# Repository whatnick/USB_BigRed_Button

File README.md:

# KiCAD port of USB Big Red Button Project
- Imported from Eagle version of files on 28/11/2020
- Added STL enclosure / PCB carries 24/12/2020
- For mechanical designs in Fusion 360 refer to original repository
- For software refer to original repository

## Renders

## Direct Order for PCB/BOM

- Order PCB via [OSHPark](https://oshpark.com/shared_projects/303OZMds)
- Order BOM via [Digikey](https://digikey.com.au/short/z10044)

## Credits

- Original design by [@bikerglen](https://twitter.com/bikerglen)
- KiCAD port by [@whatnick](https://twitter.com/whatnick)
- 3D prints by [@tweety_belle](https://twitter.com/tweety_belle) and [SANE Makerspace](http://www.sanemakerspace.com/)

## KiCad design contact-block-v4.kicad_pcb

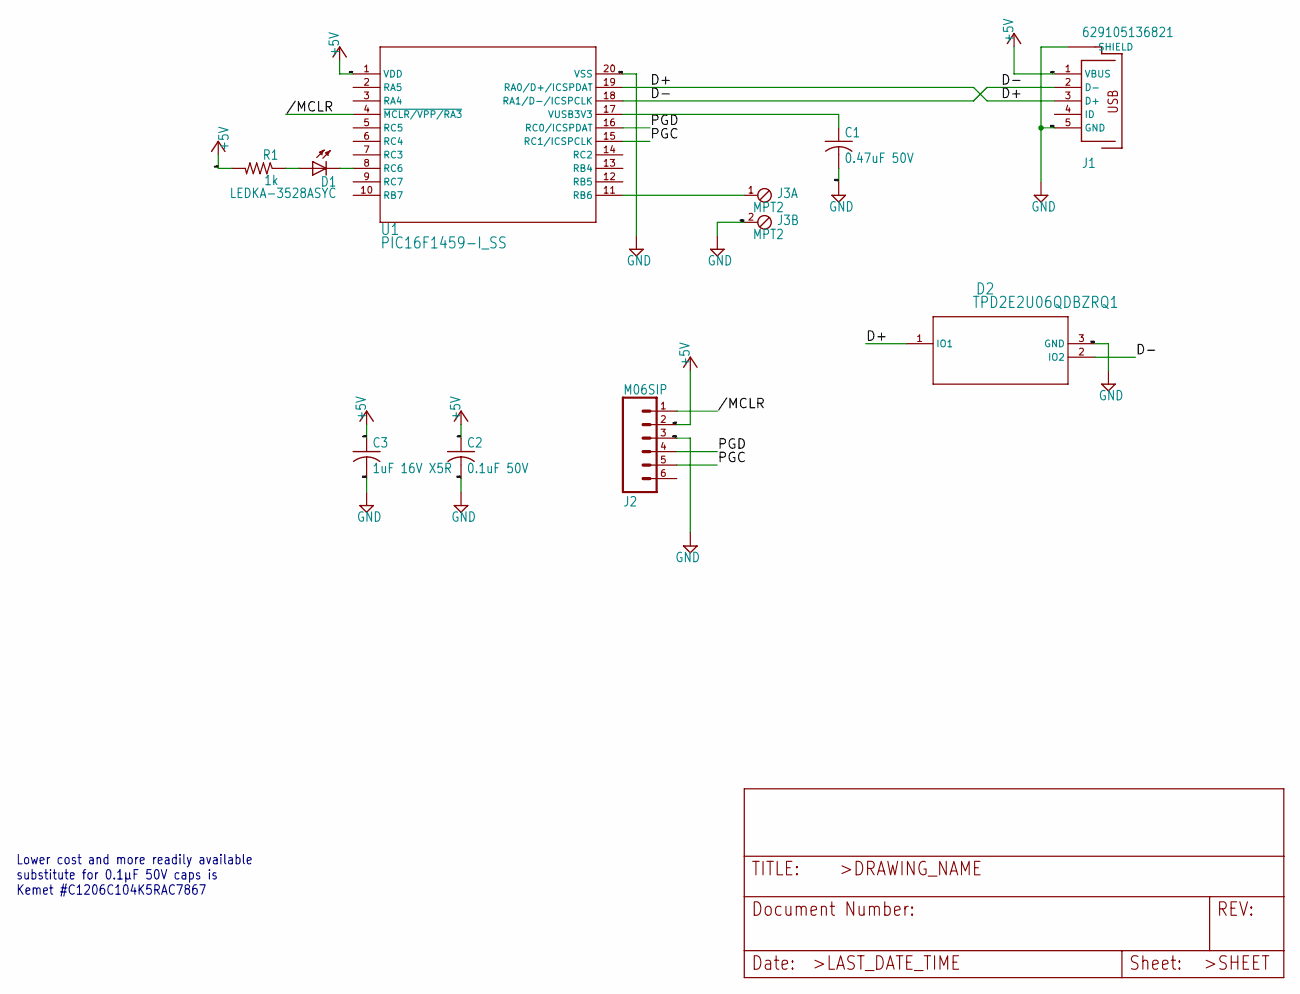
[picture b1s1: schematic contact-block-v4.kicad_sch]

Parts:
C1: C1206C474K5RACTU; C_1206_3216Metric
C2: C1206S104M5RACTU; C_1206_3216Metric
C3: C1210C105K4PACTU; C_1210_3225Metric
D1: LEDKA-3528ASYC; LED_PLCC-2
D2: TPD2E2U06QDBZRQ1; SOT-23
J1: 629105136821; WE_629105136821
J2: M06SIP; PinHeader_1x06_P2.54mm_Vertical
J3: MPT2; PinSocket_1x02_P2.54mm_Vertical
R1: CR1206-JW-102ELF; R_1206_3216Metric
U1: PIC16F1459-I_SS; SSOP-20_5.3x7.2mm_P0.65mm

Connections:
+5V: C2.1, C3.1, J1.1 (VBUS), J2.2, R1.2, U1.1 (VDD)
/D+: D2.1 (IO1), J1.3 (D+), U1.19 (RA0/D+/ICSPDAT)
/D-: D2.2 (IO2), J1.2 (D-), U1.18 (RA1/D-/ICSPCLK)
/PGC: J2.5, U1.15 (RC1/ICSPCLK)
/PGD: J2.4, U1.16 (RC0/ICSPDAT)
//MCLR: J2.1, U1.4 (~MCLR/VPP/RA3)
GND: C1.2, C2.2, C3.2, D2.3 (GND), J1.5 (GND), J1.S1 (SHIELD), J1.S2 (SHIELD), J1.S3 (SHIELD), J1.S4 (SHIELD), J2.3, J3.2 (1), U1.20 (VSS)
unnamed: C1.1, U1.17 (VUSB3V3)
unnamed: D1.1 (A), R1.1
unnamed: D1.2 (C), U1.8 (RC6)
unnamed: J3.1, U1.11 (RB6)

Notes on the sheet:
Lower cost and more readily available substitute for 0.1µF 50V caps is Kemet #C1206C104K5RAC7867

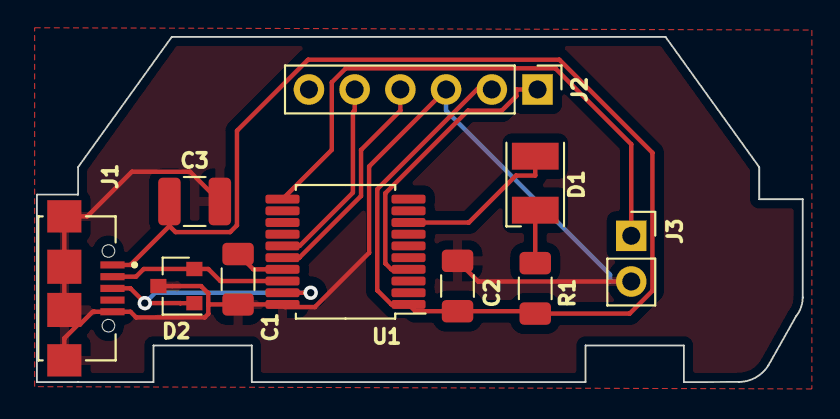
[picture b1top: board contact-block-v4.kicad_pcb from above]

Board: 2 copper layers, 42.5 x 19.2 mm, 10 parts (0 on the bottom side), 11 nets.

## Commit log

2020-11-28 Initial import
2020-11-28 Add README
2020-11-28 Complete routing and add 3d models
2020-11-28 Save schematic changes
2020-11-28 Add doc images and bom
2020-11-29 Add parts and gerbers
2020-12-23 Add enclosure/render/BOM
2021-01-17 Some updates and enclosure step
2021-01-17 Add #honks
